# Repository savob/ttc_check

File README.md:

# TTC Check

A display to show bus arrival predictions on demand in Toronto using an ESP32.

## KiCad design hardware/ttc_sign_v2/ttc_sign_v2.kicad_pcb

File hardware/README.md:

# TTC Check Hardware Files

Here are the files related to the hardware design of the TTC Check board. They are all from KiCad 7.0.10 at the oldest.

## Projects

| Project | Description |
| --- | --- |
| `ttc_sign_vX` | Different versions of the flight computer |

## Other Files and Folders

| Folder | Purpose |
| --- | --- |
| `schematics` | Has the schematics in PDF (colour and B/W) and SVG (just colour) formats |
| `ttc_sign.pretty` | Holds custom footprints needed for this project |
| `small_title_block.kicad_wks` | Has the worksheet template with a more compact titleblock |
| `ttc_sign.kicad_sym` | Holds the custom symbols used in schematics |

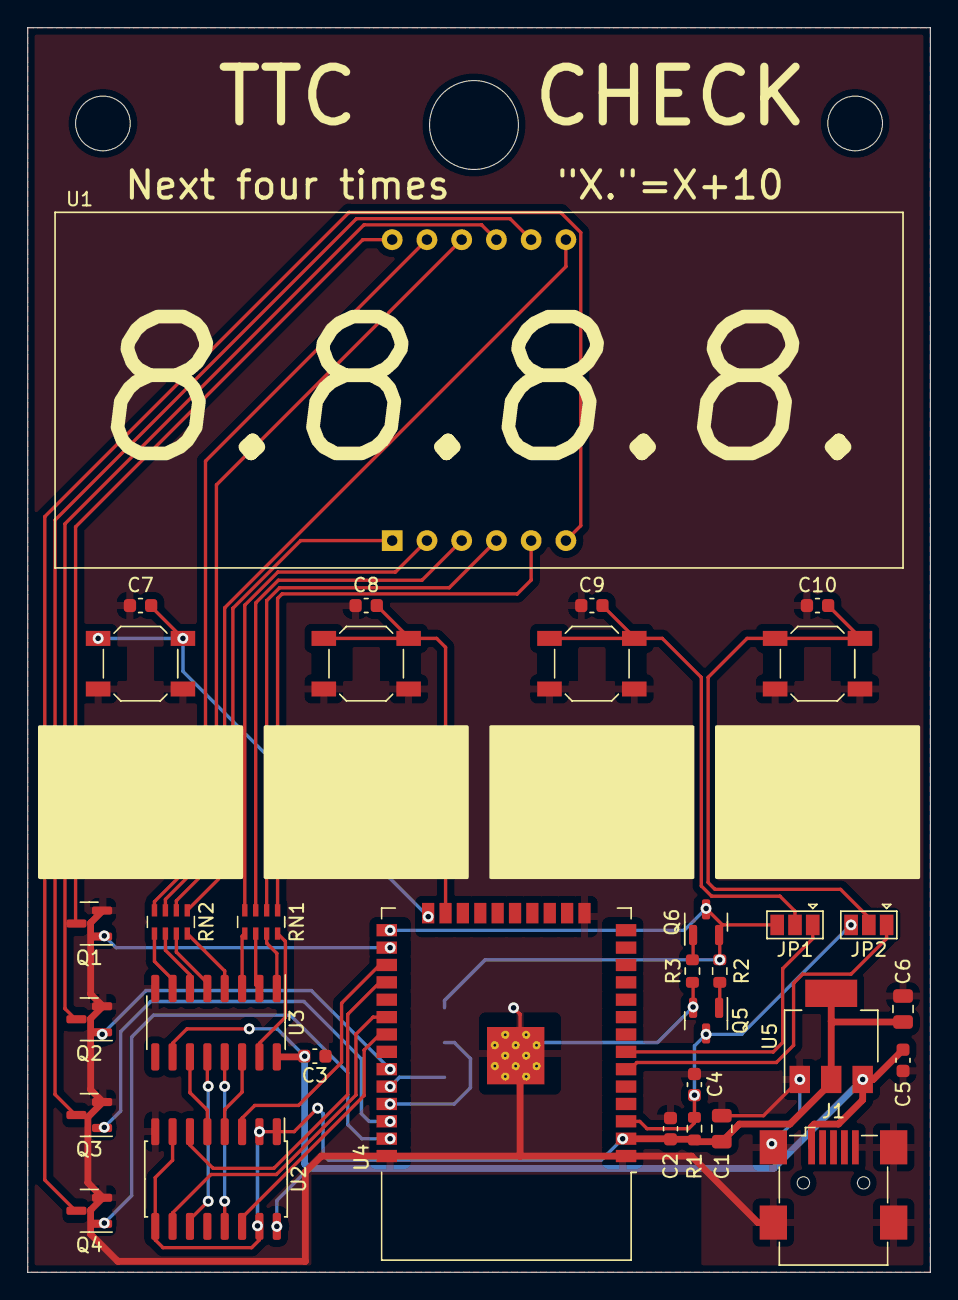
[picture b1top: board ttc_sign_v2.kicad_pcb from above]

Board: 2 copper layers, 66.0 x 91.0 mm, 37 parts (1 on the bottom side), 49 nets.

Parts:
C1, C6: 22µ; C_0805_2012Metric
C2, C3, C4, C7, C8, C9, C10: 100n; C_0603_1608Metric
C5: 10µ; C_0603_1608Metric
H1, H3: 4MM; MountingHole_4mm
H2: 6.5MM; MountingHole_6.5mm
J1: USB_B_Mini; USB_Mini-B_Wuerth_65100516121_Horizontal
J2: PROG; PinHeader_2x03_P2.54mm_Vertical_SMD
JP1: DEBUG1; SolderJumper-3_P1.3mm_Open_Pad1.0x1.5mm
JP2: DEBUG2; SolderJumper-3_P1.3mm_Open_Pad1.0x1.5mm
Q1, Q2, Q3, Q4: 2N7002; SOT-23
Q5, Q6: S8050; SOT-23
R1, R2, R3: 10k; R_0603_1608Metric
RN1, RN2: 110; R_Array_Concave_4x0603
SW1, SW2, SW3, SW4: SW_Push; SW_SPST_SKQG_WithStem
U1: DISPLAY; 7SEG4DIG20MM
U2: CD40109; SO-16_5.3x10.2mm_P1.27mm
U3: 74HC595; SOP-16_3.9x9.9mm_P1.27mm
U4: ESP32-WROOM-32D; ESP32-WROOM-32
U5: AP1117-33; SOT-223-3_TabPin2

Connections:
+3V3: C1.1, C2.2, C6.1, R1.2, U2.1 (VLOW), U2.2 (ENA), U2.7 (ENB), U2.9 (ENC), U2.15 (END), U4.2 (VDD), U5.2 (VO)
+5V: C3.1, C5.2, J1.1 (VBUS), U2.16 (VHIGH), U3.10 (~SRCLR), U3.16 (VCC), U5.3 (VI)
/A: RN2.4 (R4.1), U1.11 (A)
/B: RN2.2 (R2.1), U1.7 (B)
/BOOT: JP1.3 (B), Q6.3 (C), U4.25 (IO0)
/BUT_{1}: C7.2, SW1.2, U4.24 (IO2)
/BUT_{2}: C8.2, SW2.2, U4.23 (IO15)
/BUT_{3}: JP1.1 (A), U4.7 (IO35)
/BUT_{4}: JP2.1 (A), U4.6 (IO34)
/C: RN1.2 (R2.1), U1.4 (C)
/C_{1}: Q1.3 (D), U1.12 (CC1)
/C_{2}: Q2.3 (D), U1.9 (CC2)
/C_{3}: Q3.3 (D), U1.8 (CC3)
/C_{4}: Q4.3 (D), U1.6 (CC4)
/D: RN1.4 (R4.1), U1.2 (D)
/DIGIT_{1}: Q1.1 (G), U4.26 (IO4)
/DIGIT_{2}: Q2.1 (G), U4.33 (IO21)
/DIGIT_{3}: Q3.1 (G), U4.36 (IO22)
/DIGIT_{4}: Q4.1 (G), U4.37 (IO23)
/DP: RN1.3 (R3.1), U1.3 (DPX)
/DTR: J2.2, Q6.2 (E), R2.2
/E: RN2.1 (R1.1), U1.1 (E)
/EN: C4.2, JP2.3 (B), Q5.3 (C), R1.1, U4.3 (EN)
/F: RN2.3 (R3.1), U1.10 (F)
/G: RN1.1 (R1.1), U1.5 (G)
/OE: U2.14 (IND), U4.31 (IO19)
/OE_{5V}: U2.13 (OUTD), U3.13 (~OE)
/RCLK: U2.10 (INC), U4.30 (IO18)
/RCLK_{5V}: U2.11 (OUTC), U3.12 (RCLK)
/RTS: J2.3, Q5.2 (E), R3.2
/RX: J2.6, U4.34 (RXD0/IO3)
/SER: U2.3 (INA), U4.27 (IO16)
/SER_{5V}: U2.4 (OUTA), U3.14 (SER)
/SRCLCK: U2.6 (INB), U4.28 (IO17)
/SRCLK_{5V}: U2.5 (OUTB), U3.11 (SRCLK)
/SW_{3}: C9.2, JP1.2 (C), SW3.2
/SW_{4}: C10.2, JP2.2 (C), SW4.2
/TX: J2.4, U4.35 (TXD0/IO1)
GND: C1.2, C2.1, C3.2, C4.1, C5.1, C6.2, C7.1, C8.1, C9.1, C10.1, J1.5 (GND), J1.6 (Shield), J2.1, Q1.2 (S), Q2.2 (S), Q3.2 (S), Q4.2 (S), SW1.1, SW2.1, SW3.1, SW4.1, U2.8 (GND), U3.8 (GND), U4.1 (GND), U4.15 (GND), U4.38 (GND), U4.39 (GND), U5.1 (GND)
unnamed: Q5.1 (B), R2.1
unnamed: Q6.1 (B), R3.1
unnamed: RN1.5 (R4.2), U3.3 (QD)
unnamed: RN1.6 (R3.2), U3.2 (QC)
unnamed: RN1.7 (R2.2), U3.1 (QB)
unnamed: RN1.8 (R1.2), U3.15 (QA)
unnamed: RN2.5 (R4.2), U3.7 (QH)
unnamed: RN2.6 (R3.2), U3.6 (QG)
unnamed: RN2.7 (R2.2), U3.5 (QF)
unnamed: RN2.8 (R1.2), U3.4 (QE)

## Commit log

2022-03-15 Ignore wifiInfo.h header
2022-03-15 Initial upload of all project code
    Uploaded code both past and present, scrubbed of WiFi details this time
2022-03-15 Upload of original hardware files
    Uploaded the hardware files used to manufacture the first set of boards (V1.1). Only changes to these since manufacture is the addition of notes in 1.2 from 1.1.
2024-01-08 Moved firmware
2024-01-08 Moved and uploaded hardware files
2024-01-08 Added `.gitignore` for hardware
2024-01-08 Touched up main readme
